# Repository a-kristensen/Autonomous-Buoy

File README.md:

# Autonomous-Buoy
This project was conducted at Sønderborg SDU 2017-2018.
It was the MDB2 project where the goal was to improve a sailbuoy, built in the previous projects.

The contents of this repository is:
- Embedded software
- PC GUI software
- Hardware implementation

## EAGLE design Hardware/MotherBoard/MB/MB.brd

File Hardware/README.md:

This folder contains the Eagle projects created for the hardware implimentation

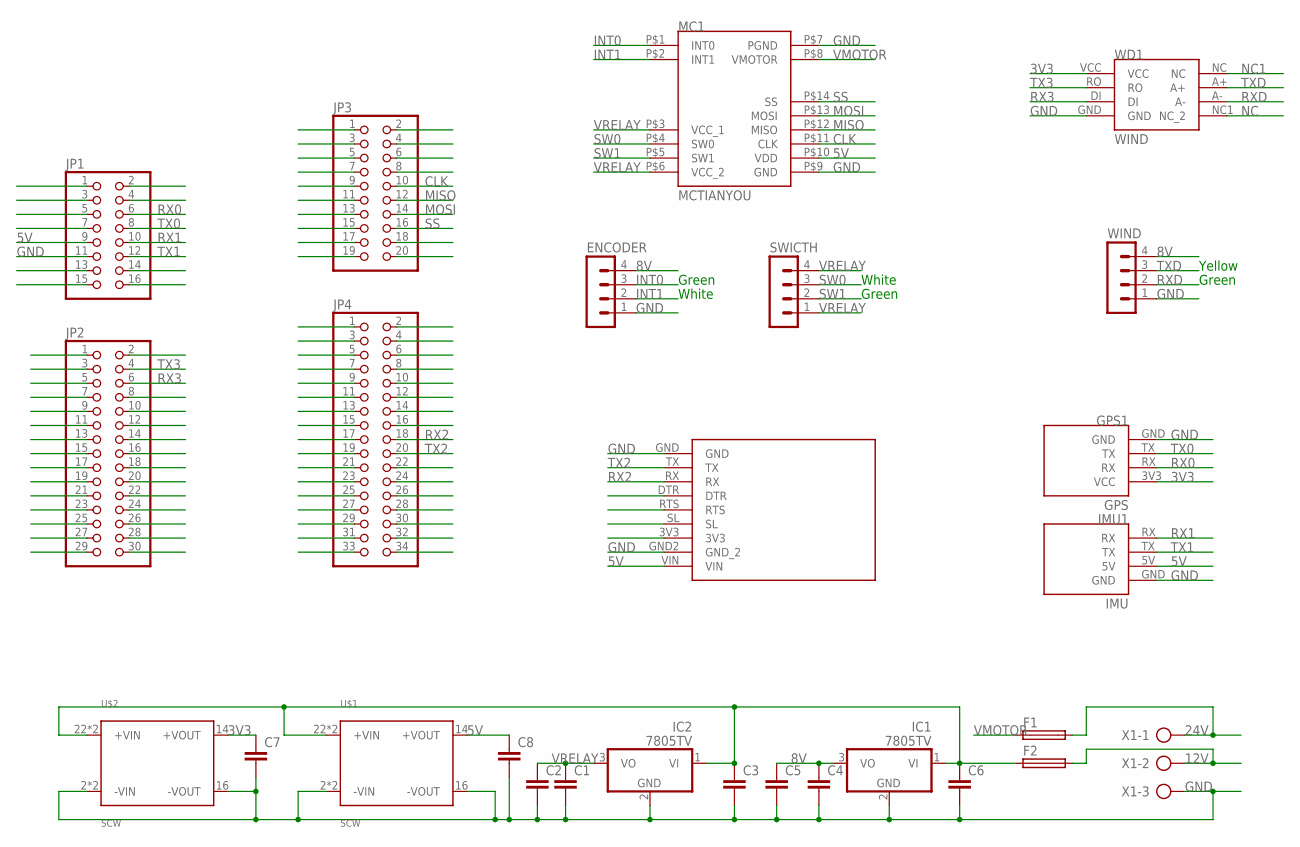
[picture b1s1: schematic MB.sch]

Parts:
C1, C2, C3, C4, C5, C6, C7, C8: C-EUC0603; C0603
ENCODER: MA04-1
F1, F2: SH22,5
GPS1: GPS
IC1, IC2: 7805TV; TO220V
IMU1: IMU
JP1: PINHD-2X8; 2X08
JP2: PINHD-2X15; 2X15
JP3: PINHD-2X10; 2X10
JP4: PINHD-2X17; 2X17
MC1: MCTIANYOU
SWICTH: MA04-1
U$1, U$2: SCW
WD1: WIND
WIND: MA04-1
X1: AK300/3
XBEE1: XBEE

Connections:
3V3: C7.1, GPS1.3V3 (VCC), U$2.14 (+VOUT), WD1.VCC
5V: C8.1, IMU1.5V, JP1.9, MC1.P$10 (VDD), U$1.14 (+VOUT), XBEE1.VIN
8V: C4.1, C5.1, ENCODER.4, IC1.3 (VO), WIND.4
12V: F2.2, X1.2
24V: F1.2, X1.1
CLK: JP3.10, MC1.P$11 (CLK)
GND: C1.2, C2.2, C3.2, C4.2, C5.2, C6.2, C7.2, C8.2, ENCODER.1, GPS1.GND, IC1.2 (GND), IC2.2 (GND), IMU1.GND, JP1.11, MC1.P$7 (PGND), MC1.P$9 (GND), U$1.2 (-VIN), U$1.3 (-VIN), U$1.16 (-VOUT), U$2.2 (-VIN), U$2.3 (-VIN), U$2.16 (-VOUT), WD1.GND, WIND.1, X1.3, XBEE1.GND, XBEE1.GND2 (GND_2)
INT0: ENCODER.3, MC1.P$1 (INT0)
INT1: ENCODER.2, MC1.P$2 (INT1)
MISO: JP3.12, MC1.P$12 (MISO)
MOSI: JP3.14, MC1.P$13 (MOSI)
unnamed: C3.1, C6.1, F2.1, IC1.1 (VI), IC2.1 (VI), U$1.22 (+VIN), U$1.23 (+VIN), U$2.22 (+VIN), U$2.23 (+VIN)
NC: WD1.NC1 (NC_2)
NC1: WD1.NC
RX0: GPS1.RX, JP1.6
RX1: IMU1.RX, JP1.10
RX2: JP4.18, XBEE1.RX
RX3: JP2.6, WD1.DI
RXD: WD1.A-, WIND.2
SS: JP3.16, MC1.P$14 (SS)
SW0: MC1.P$4 (SW0), SWICTH.3
SW1: MC1.P$5 (SW1), SWICTH.2
TX0: GPS1.TX, JP1.8
TX1: IMU1.TX, JP1.12
TX2: JP4.20, XBEE1.TX
TX3: JP2.4, WD1.RO
TXD: WD1.A+, WIND.3
VMOTOR: F1.1, MC1.P$8 (VMOTOR)
VRELAY: C1.1, C2.1, IC2.3 (VO), MC1.P$3 (VCC_1), MC1.P$6 (VCC_2), SWICTH.1, SWICTH.4

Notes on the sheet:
Green
Yellow
White

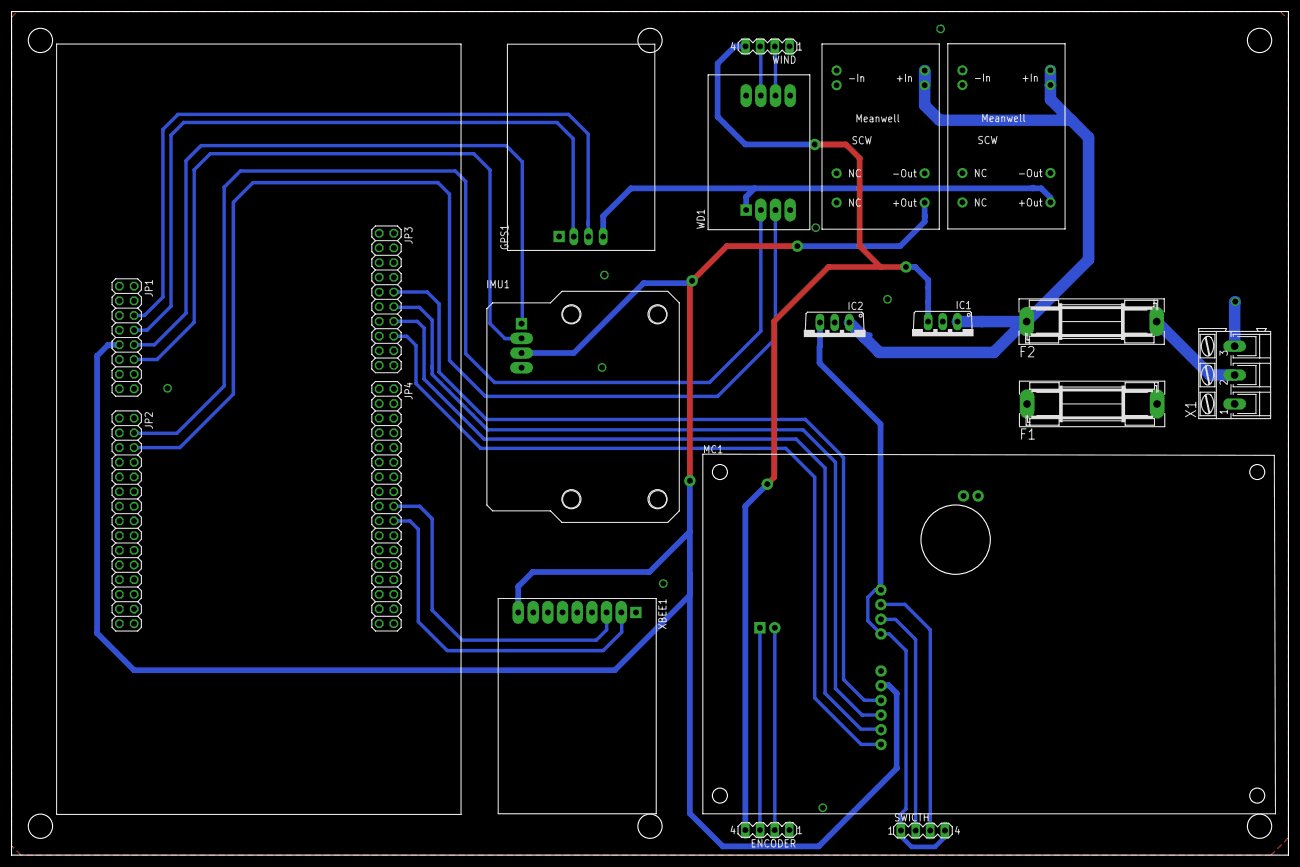
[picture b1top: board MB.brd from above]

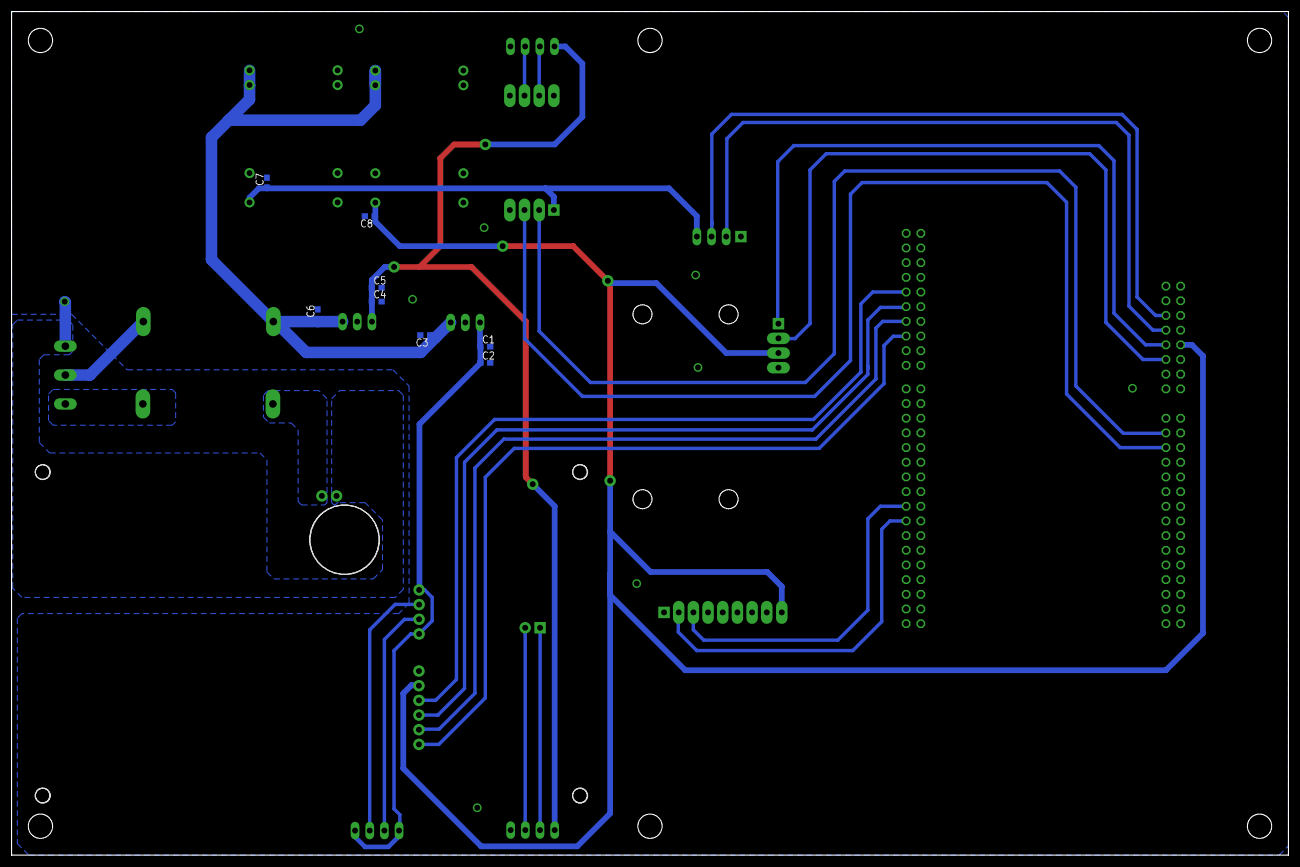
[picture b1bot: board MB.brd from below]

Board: 2 copper layers, 221.0 x 146.0 mm, 27 parts (8 on the bottom side), 27 nets.

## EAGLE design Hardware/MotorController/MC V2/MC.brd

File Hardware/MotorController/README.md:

This folder contains a project in Eagle for hardware implementation of motor controller and also a project in Arduino for controling the hardware.

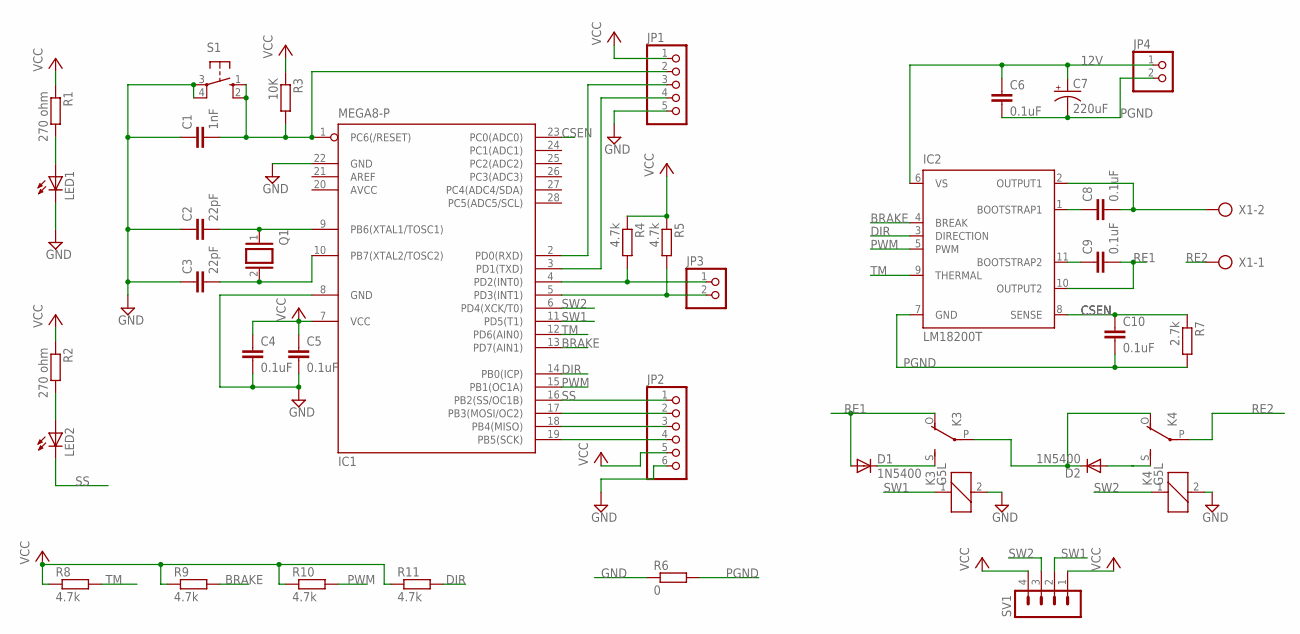
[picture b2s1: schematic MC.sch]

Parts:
C1: 1nF; C0603
C2, C3: 22pF; C0603
C4, C5, C6, C8, C9, C10: 0.1uF; C0603
C7: 220uF; PANASONIC_F
D1, D2: 1N5400; DO201-15
IC1: MEGA8-P; DIL28-3
IC2: LM18200T; TO-220-11
JP1: PINHD-1X5; 1X05
JP2: PINHD-1X6; 1X06
JP3, JP4: PINHD-1X2; 1X02
K3, K4: G5L; G5LE
LED1, LED2: LEDSML0603; SML0603
Q1: XTAL/S; QS
R1, R2: 270 ohm; R0805
R3: 10K; R0805
R4, R5, R8, R9, R11: 4.7k; R0805
R6: 0; R0603
R7: 2.7k; R0805
R10: 4.7k; 0204/7
S1: 10-XX; B3F-10XX
SV1: MA04-1
X1: AK300/2

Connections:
12V: C6.1, C7.+, IC2.6 (VS), JP4.1
AVCC: IC1.20 (AVCC)
BRAKE: IC1.13 (PD7(AIN1)), IC2.4 (BREAK), R9.2
CSEN: C10.1, IC1.23 (PC0(ADC0)), IC2.8 (SENSE), R7.1
DIR: IC1.14 (PB0(ICP)), IC2.3 (DIRECTION), R11.2
GND: C1.1, C2.1, C3.1, C4.2, C5.2, IC1.8 (GND), IC1.22 (GND), JP1.5, JP2.6, K3.2, K4.2, LED1.C, R6.1, S1.3, S1.4 (P1)
unnamed: IC1.4 (PD2(INT0)), JP3.1, R4.2
unnamed: C3.2, IC1.10 (PB7(XTAL2/TOSC2)), Q1.2
unnamed: IC1.17 (PB3(MOSI/OC2)), JP2.2
unnamed: IC1.18 (PB4(MISO)), JP2.3
unnamed: LED1.A, R1.2
unnamed: C8.2, IC2.2 (OUTPUT1), X1.2
unnamed: IC1.5 (PD3(INT1)), JP3.2, R5.2
unnamed: IC1.19 (PB5(SCK)), JP2.4
unnamed: D1.C, K3.S
unnamed: IC1.2 (PD0(RXD)), JP1.3
unnamed: IC1.3 (PD1(TXD)), JP1.4
unnamed: C2.2, IC1.9 (PB6(XTAL1/TOSC1)), Q1.1
unnamed: C8.1, IC2.1 (BOOTSTRAP1)
unnamed: D2.C, K3.P, K4.O
unnamed: D2.A, K4.S
unnamed: C9.1, IC2.11 (BOOTSTRAP2)
unnamed: C1.2, IC1.1 (PC6(/RESET)), JP1.2, R3.2, S1.1 (S), S1.2 (S1)
unnamed: LED2.A, R2.2
PGND: C6.2, C7.-, C10.2, IC2.7 (GND), JP4.2, R6.2, R7.2
PWM: IC1.15 (PB1(OC1A)), IC2.5 (PWM), R10.2
RE1: C9.2, D1.A, IC2.10 (OUTPUT2), K3.O
RE2: K4.P, X1.1
SS: IC1.16 (PB2(SS/OC1B)), JP2.1, LED2.C
SW1: IC1.11 (PD5(T1)), K3.1, SV1.2
SW2: IC1.6 (PD4(XCK/T0)), K4.1, SV1.3
TM: IC1.12 (PD6(AIN0)), IC2.9 (THERMAL), R8.2
VCC: C4.1, C5.1, IC1.7 (VCC), JP1.1, JP2.5, R1.1, R2.1, R3.1, R4.1, R5.1, R8.1, R9.1, R10.1, R11.1, SV1.1, SV1.4

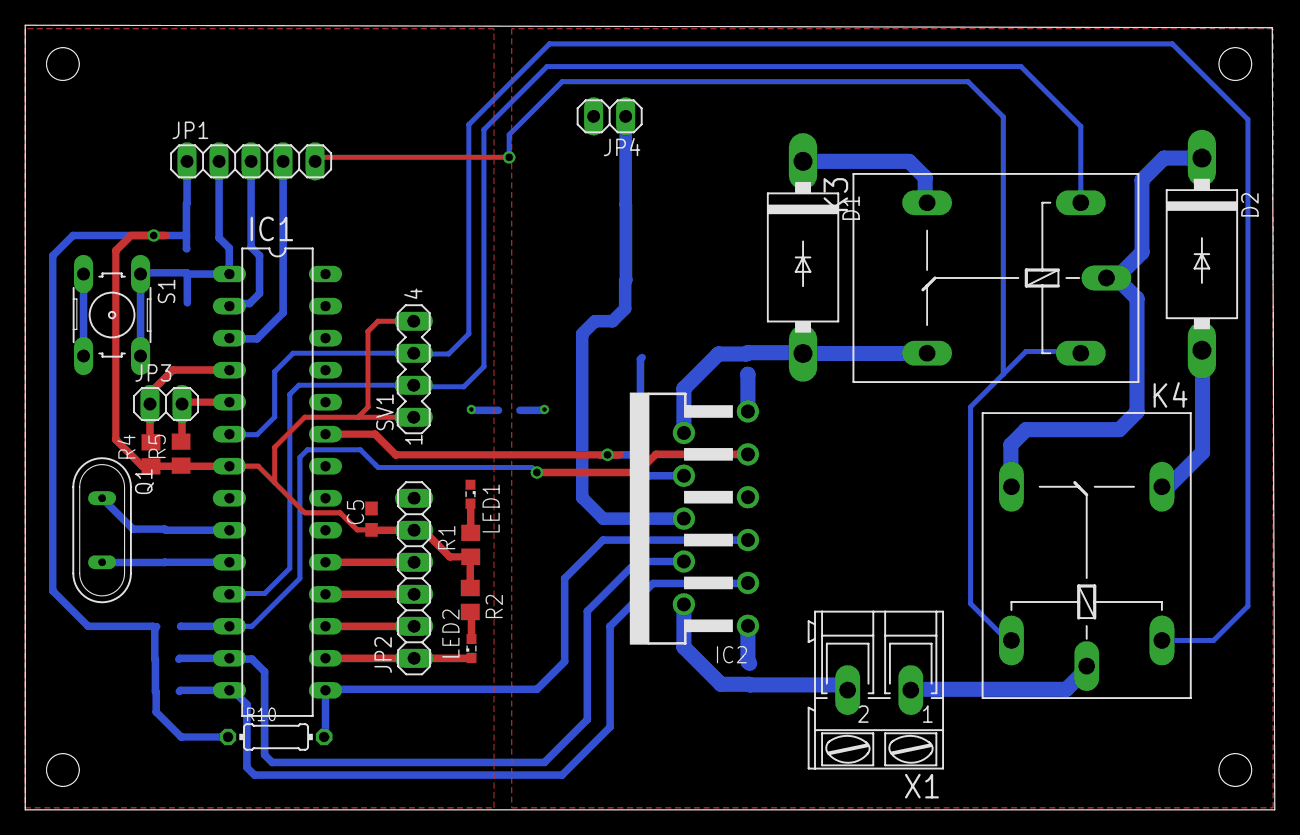
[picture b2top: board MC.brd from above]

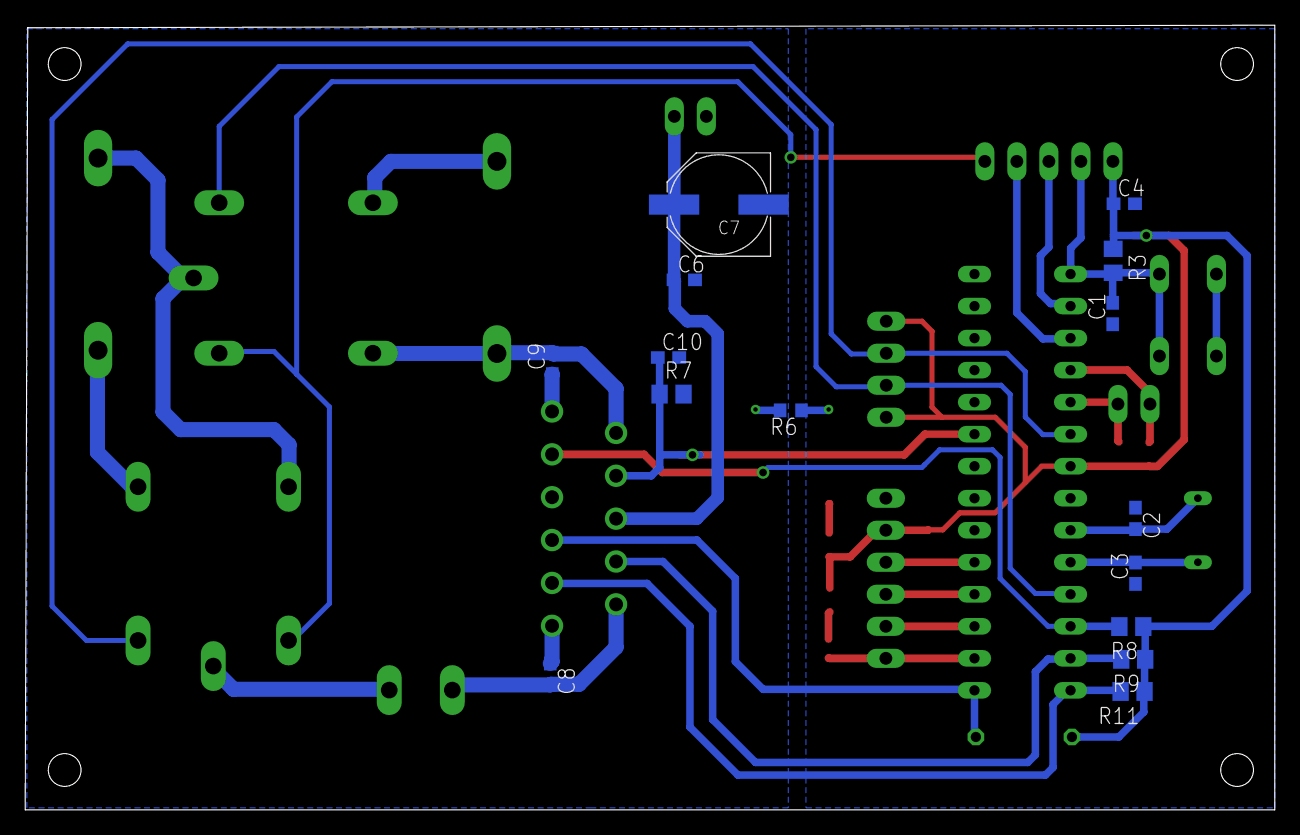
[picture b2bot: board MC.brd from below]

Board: 2 copper layers, 99.1 x 62.2 mm, 37 parts (15 on the bottom side), 32 nets.
